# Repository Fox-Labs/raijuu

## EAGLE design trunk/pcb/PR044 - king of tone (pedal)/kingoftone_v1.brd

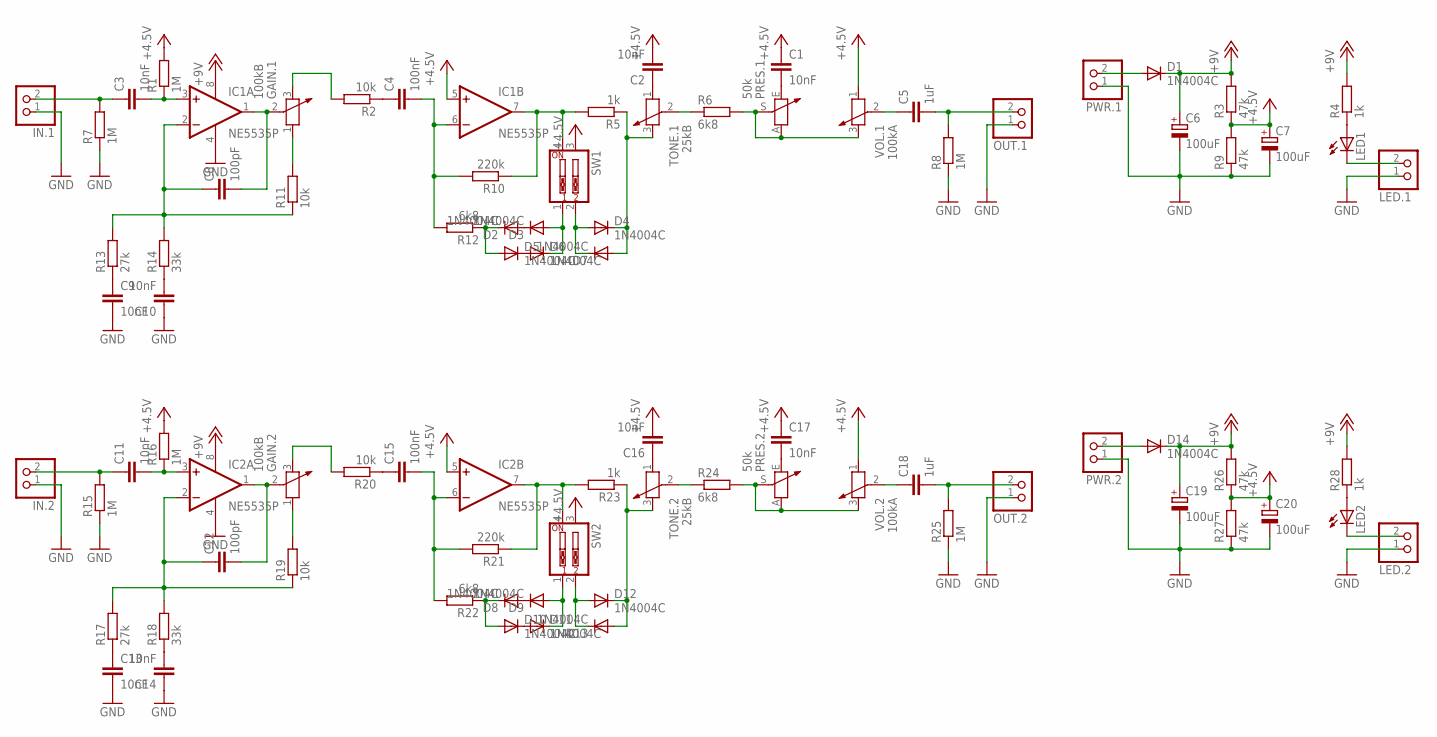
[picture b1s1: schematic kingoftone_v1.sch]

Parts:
C1, C2, C3, C9, C10, C11, C13, C14, C16, C17: 10nF; C050-025X075
C4, C15: 100nF; C050-025X075
C5, C18: 1uF; C050-025X075
C6, C7, C19, C20: 100uF; E2,5-6
C8, C12: 100pF; C050-025X075
D1, D2, D3, D4, D5, D6, D7, D8, D9, D10, D11, D12, D13, D14: 1N4004C; DO41-5
GAIN.1, GAIN.2: 100kB; 1X03
IC1, IC2: NE5535P; DIL08
IN.1, IN.2: PINHD-1X2; 1X02
LED1, LED2: LED3MM
LED.1, LED.2: PINHD-1X2; 1X02
OUT.1, OUT.2: PINHD-1X2; 1X02
PRES.1, PRES.2: 50k; CT6
PWR.1, PWR.2: PINHD-1X2; 1X02
R1, R7, R8, R15, R16, R25: 1M; 0207/5V
R2, R11, R19, R20: 10k; 0207/5V
R3, R9, R26, R27: 47k; 0207/5V
R4, R5, R23, R28: 1k; 0207/5V
R6, R12, R22, R24: 6k8; 0207/5V
R10, R21: 220k; 0207/5V
R13, R17: 27k; 0207/5V
R14, R18: 33k; 0207/5V
SW1, SW2: SW_DIP-2; EDG-02
TONE.1, TONE.2: 25kB; 1X03
VOL.1, VOL.2: 100kA; 1X03

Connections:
+4.5V: C1.1, C2.2, C7.+, C16.2, C17.1, C20.+, IC1.5 (+IN), IC2.5 (+IN), R1.2, R3.1, R9.2, R16.2, R26.1, R27.2, SW1.3, SW2.3, VOL.1.1, VOL.2.1
+9V: C6.+, C19.+, D1.C, D14.C, IC1.8 (V+), IC2.8 (V+), R3.2, R4.2, R26.2, R28.2
GND: C6.-, C7.-, C9.2, C10.1, C13.2, C14.1, C19.-, C20.-, IC1.4 (V-), IC2.4 (V-), IN.1.1, IN.2.1, LED.1.1, LED.2.1, OUT.1.1, OUT.2.1, PWR.1.1, PWR.2.1, R7.1, R8.1, R9.1, R15.1, R25.1, R27.1
unnamed: C3.1, IN.1.2, R7.2
unnamed: C3.2, IC1.3 (+IN), R1.1
unnamed: C8.1, IC1.2 (-IN), R11.1, R13.2, R14.2
unnamed: C8.2, GAIN.1.2 (3), IC1.1 (OUT)
unnamed: C9.1, R13.1
unnamed: C10.2, R14.1
unnamed: GAIN.1.1, R11.2
unnamed: C4.1, R2.1
unnamed: GAIN.1.3 (2), R2.2
unnamed: C4.2, IC1.6 (-IN), R10.2, R12.2
unnamed: IC1.7 (OUT), R5.2, R10.1, SW1.4
unnamed: D2.A, D3.C
unnamed: D2.C, D5.A, R12.1
unnamed: D5.C, D6.A
unnamed: D3.A, D6.C, SW1.1
unnamed: D4.C, D7.A, R5.1, TONE.1.3 (2)
unnamed: D4.A, D7.C, SW1.2
unnamed: C5.1, VOL.1.2 (3)
unnamed: R6.1, TONE.1.2 (3)
unnamed: C2.1, TONE.1.1
unnamed: C1.2, PRES.1.E (2)
unnamed: PRES.1.A (1), PRES.1.S (3), R6.2, VOL.1.3 (2)
unnamed: C5.2, OUT.1.2, R8.2
unnamed: D1.A, PWR.1.2
unnamed: LED1.A, R4.1
unnamed: LED1.K (C), LED.1.2
unnamed: C11.1, IN.2.2, R15.2
unnamed: C11.2, IC2.3 (+IN), R16.1
unnamed: C12.1, IC2.2 (-IN), R17.2, R18.2, R19.1
unnamed: C12.2, GAIN.2.2 (3), IC2.1 (OUT)
unnamed: C13.1, R17.1
unnamed: C14.2, R18.1
unnamed: GAIN.2.1, R19.2
unnamed: C15.1, R20.1
unnamed: GAIN.2.3 (2), R20.2
unnamed: C15.2, IC2.6 (-IN), R21.2, R22.2
unnamed: IC2.7 (OUT), R21.1, R23.2, SW2.4
unnamed: D8.A, D9.C
unnamed: D8.C, D10.A, R22.1
unnamed: D10.C, D11.A
unnamed: D9.A, D11.C, SW2.1
unnamed: D12.A, D13.C, SW2.2
unnamed: R24.1, TONE.2.2 (3)
unnamed: C16.1, TONE.2.1
unnamed: C17.2, PRES.2.E (2)
unnamed: PRES.2.A (1), PRES.2.S (3), R24.2, VOL.2.3 (2)
unnamed: D12.C, D13.A, R23.1, TONE.2.3 (2)
unnamed: C18.1, VOL.2.2 (3)
unnamed: C18.2, OUT.2.2, R25.2
unnamed: D14.A, PWR.2.2
unnamed: LED2.A, R28.1
unnamed: LED2.K (C), LED.2.2

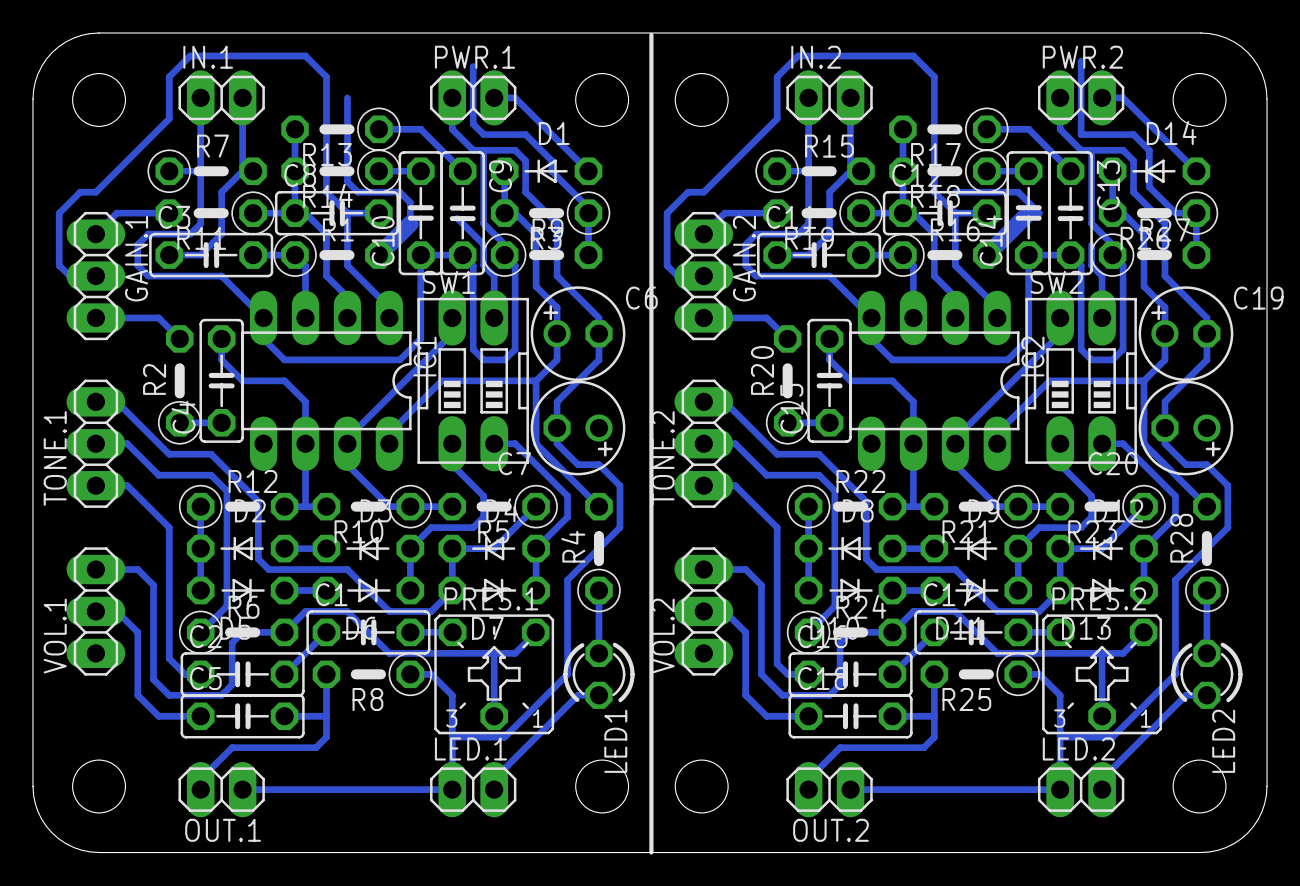
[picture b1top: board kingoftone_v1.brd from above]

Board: 2 copper layers, 74.8 x 49.6 mm, 84 parts (0 on the bottom side), 55 nets.

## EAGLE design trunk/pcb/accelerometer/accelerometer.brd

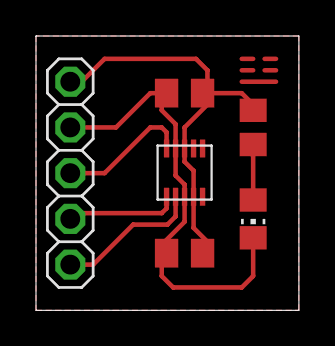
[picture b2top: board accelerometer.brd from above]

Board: 2 copper layers, 14.6 x 15.2 mm, 6 parts (0 on the bottom side), 6 nets.

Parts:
C1, C2: C0805K
JP1: 1X05
LED1: CHIP-LED0805
R1: R0805
U$1: MMA7660DFN-10-HAND; DFN-10-HAND

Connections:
+3V3: C1.1, C2.1, JP1.5, R1.2, U$1.P$3, U$1.P$9
/INT: JP1.3, U$1.P$5
GND: C1.2, C2.2, JP1.4, LED1.C, U$1.P$4, U$1.P$8
unnamed: LED1.A, R1.1
SCL: JP1.2, U$1.P$6
SDA: JP1.1, U$1.P$7

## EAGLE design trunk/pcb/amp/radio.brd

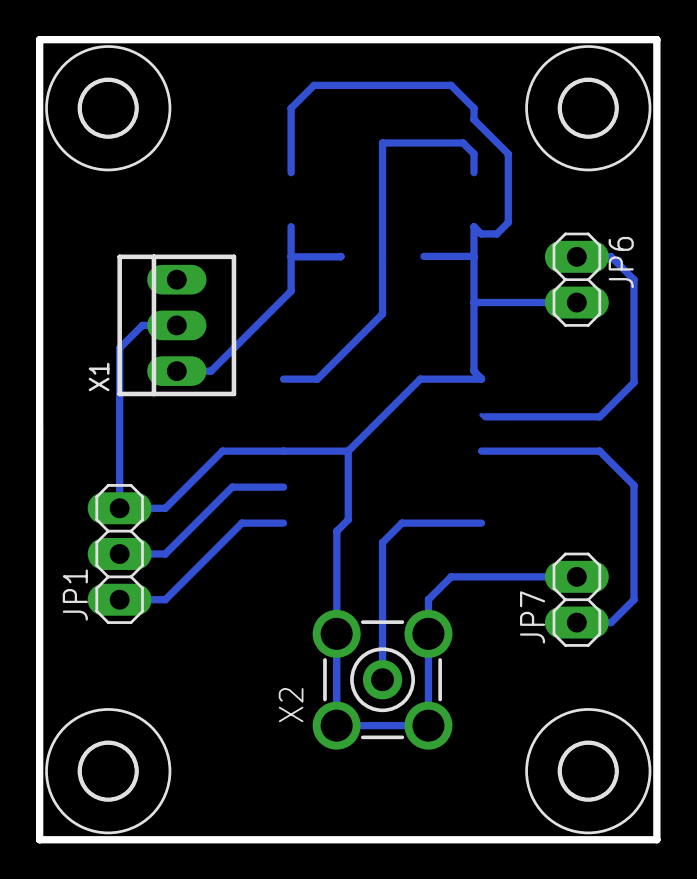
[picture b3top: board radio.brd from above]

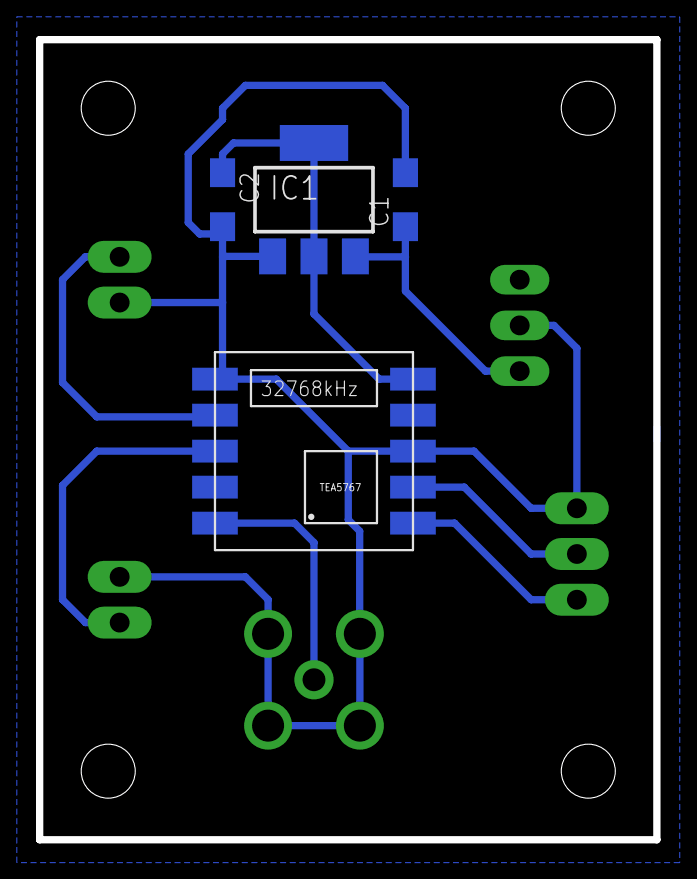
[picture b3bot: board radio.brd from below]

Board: 2 copper layers, 34.3 x 44.5 mm, 13 parts (4 on the bottom side), 8 nets.

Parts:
C1, C2: SMC_A
IC1: LM1117S; SOT223
JP1: 1X03
JP6, JP7: 1X02
U1: TEA5767
U$1, U$2, U$3, U$4: 3,0
X1: 22-23-2031
X2: BU-SMA-V

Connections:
+3V3: C2.+, IC1.2, IC1.4, U1.5
+12V: C1.+, IC1.3, X1.1
GND: C1.-, C2.-, IC1.1, JP1.3, JP6.2, JP7.2, U1.3, U1.6, X1.2, X2.2, X2.3, X2.4, X2.5
unnamed: U1.10, X2.1
OUT_L: JP6.1, U1.7
OUT_R: JP7.1, U1.8
SCL: JP1.2, U1.2
SDA: JP1.1, U1.1

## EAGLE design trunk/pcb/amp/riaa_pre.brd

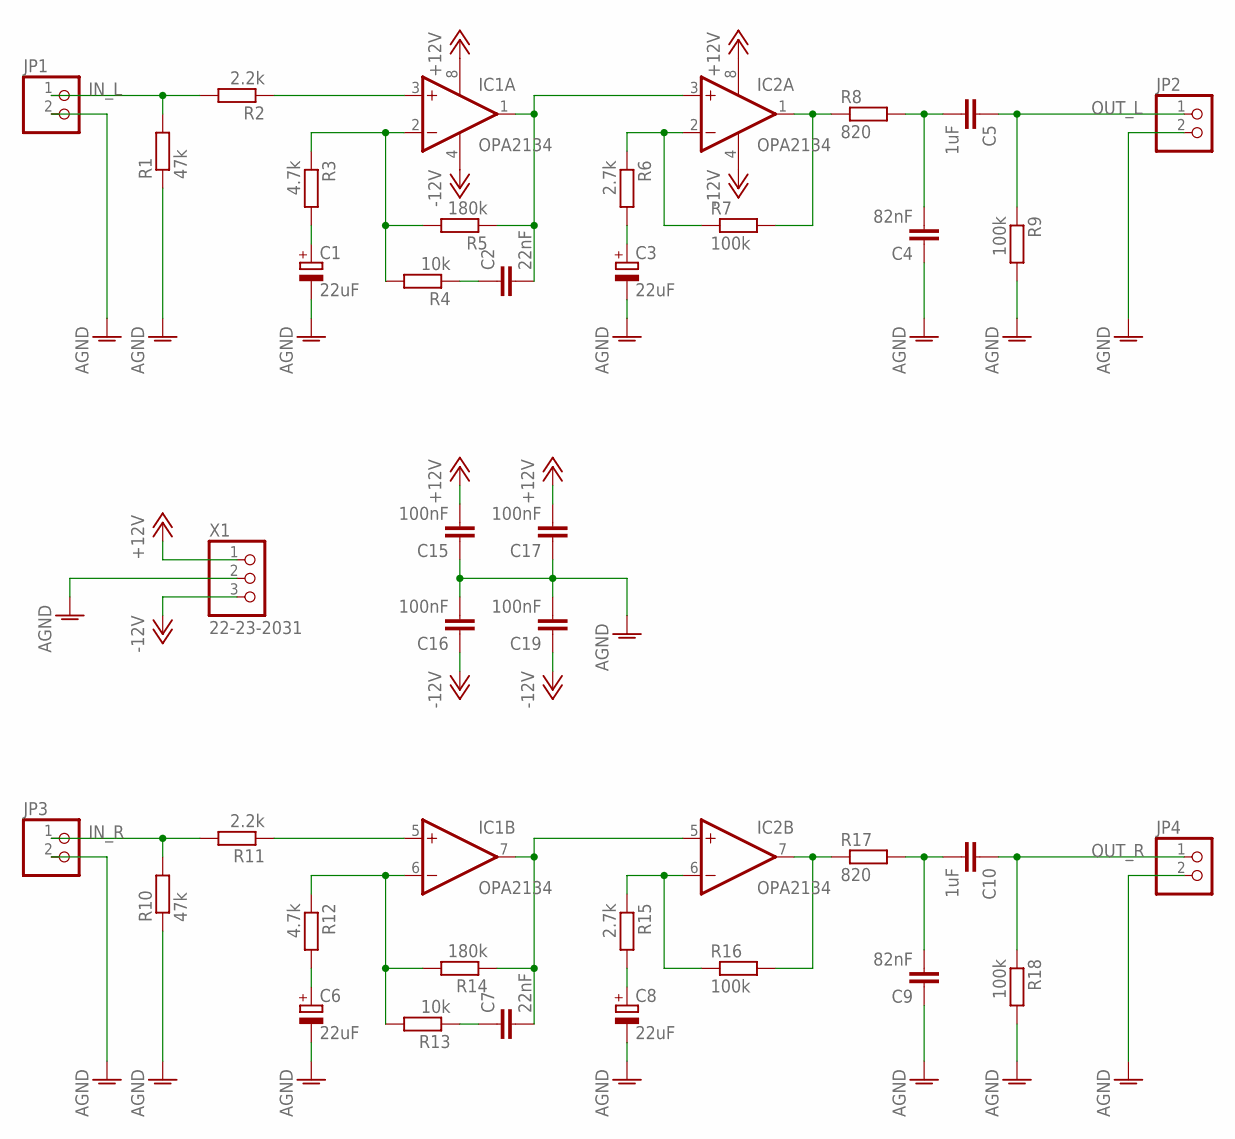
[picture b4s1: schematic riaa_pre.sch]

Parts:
C1, C3, C6, C8: 22uF; E2,5-6
C2, C7: 22nF; C050-025X075
C4, C9: 82nF; C050-025X075
C5, C10: 1uF; C050-025X075
C15, C16, C17, C19: 100nF; C050-025X075
IC1, IC2: OPA2134; DIL08
JP1, JP2, JP3, JP4: PINHD-1X2; 1X02
R1, R10: 47k; 0207/7
R2, R11: 2.2k; 0207/7
R3, R12: 4.7k; 0207/7
R4, R13: 10k; 0207/7
R5, R14: 180k; 0207/7
R6, R15: 2.7k; 0207/7
R7, R9, R16, R18: 100k; 0207/7
R8, R17: 820; 0207/7
X1: 22-23-2031

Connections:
+12V: C15.2, C17.2, IC1.8 (V+), IC2.8 (V+), X1.1
-12V: C16.1, C19.1, IC1.4 (V-), IC2.4 (V-), X1.3
AGND: C1.-, C3.-, C4.1, C6.-, C8.-, C9.1, C15.1, C16.2, C17.1, C19.2, JP1.2, JP2.2, JP3.2, JP4.2, R1.1, R9.2, R10.1, R18.2, X1.2
IN_L: JP1.1, R1.2, R2.2
IN_R: JP3.1, R10.2, R11.2
unnamed: C3.+, R6.2
unnamed: IC1.3 (+IN), R2.1
unnamed: C2.2, IC1.1 (OUT), IC2.3 (+IN), R5.1
unnamed: C4.2, C5.2, R8.2
unnamed: C2.1, R4.1
unnamed: IC1.2 (-IN), R3.1, R4.2, R5.2
unnamed: IC2.6 (-IN), R15.1, R16.1
unnamed: IC2.7 (OUT), R16.2, R17.1
unnamed: IC1.5 (+IN), R11.1
unnamed: C7.2, IC1.7 (OUT), IC2.5 (+IN), R14.1
unnamed: C7.1, R13.1
unnamed: IC1.6 (-IN), R12.1, R13.2, R14.2
unnamed: C6.+, R12.2
unnamed: C8.+, R15.2
unnamed: C9.2, C10.2, R17.2
unnamed: IC2.2 (-IN), R6.1, R7.1
unnamed: IC2.1 (OUT), R7.2, R8.1
unnamed: C1.+, R3.2
OUT_L: C5.1, JP2.1, R9.1
OUT_R: C10.1, JP4.1, R18.1

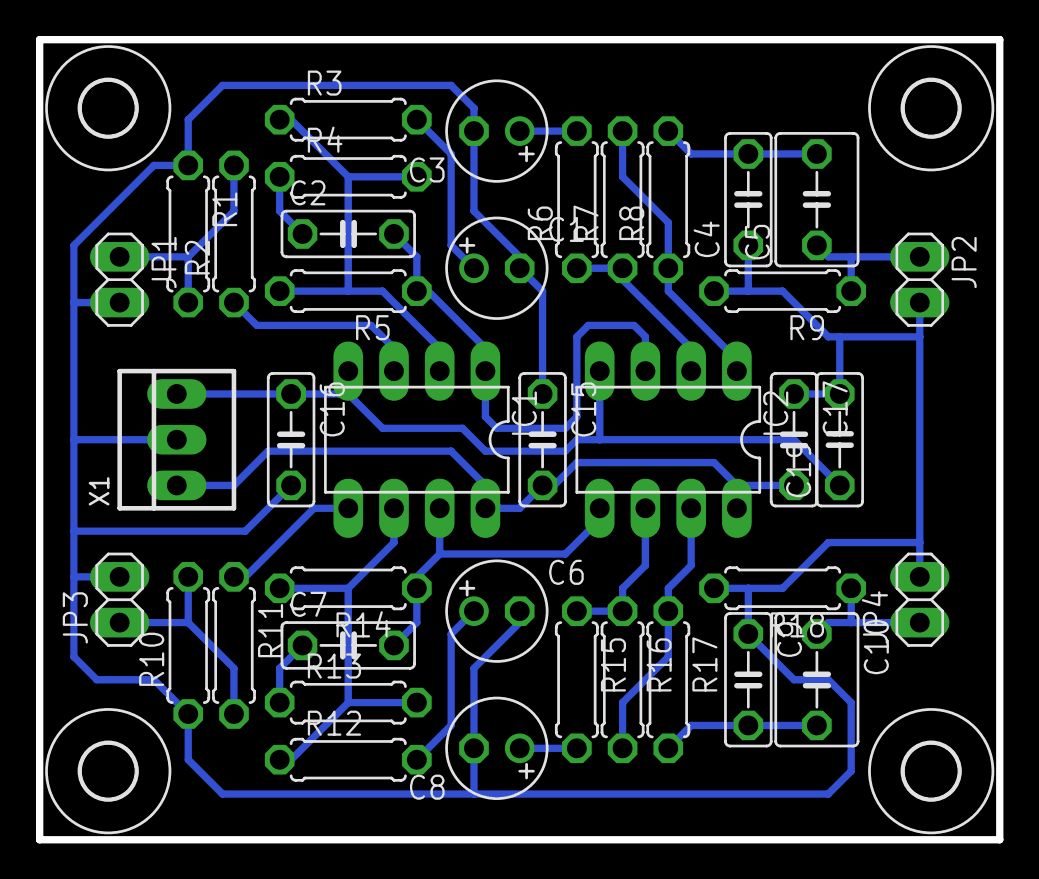
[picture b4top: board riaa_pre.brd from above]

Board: 2 copper layers, 53.3 x 44.5 mm, 43 parts (0 on the bottom side), 25 nets.

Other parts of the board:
U$1, U$2, U$3, U$4: 3,0

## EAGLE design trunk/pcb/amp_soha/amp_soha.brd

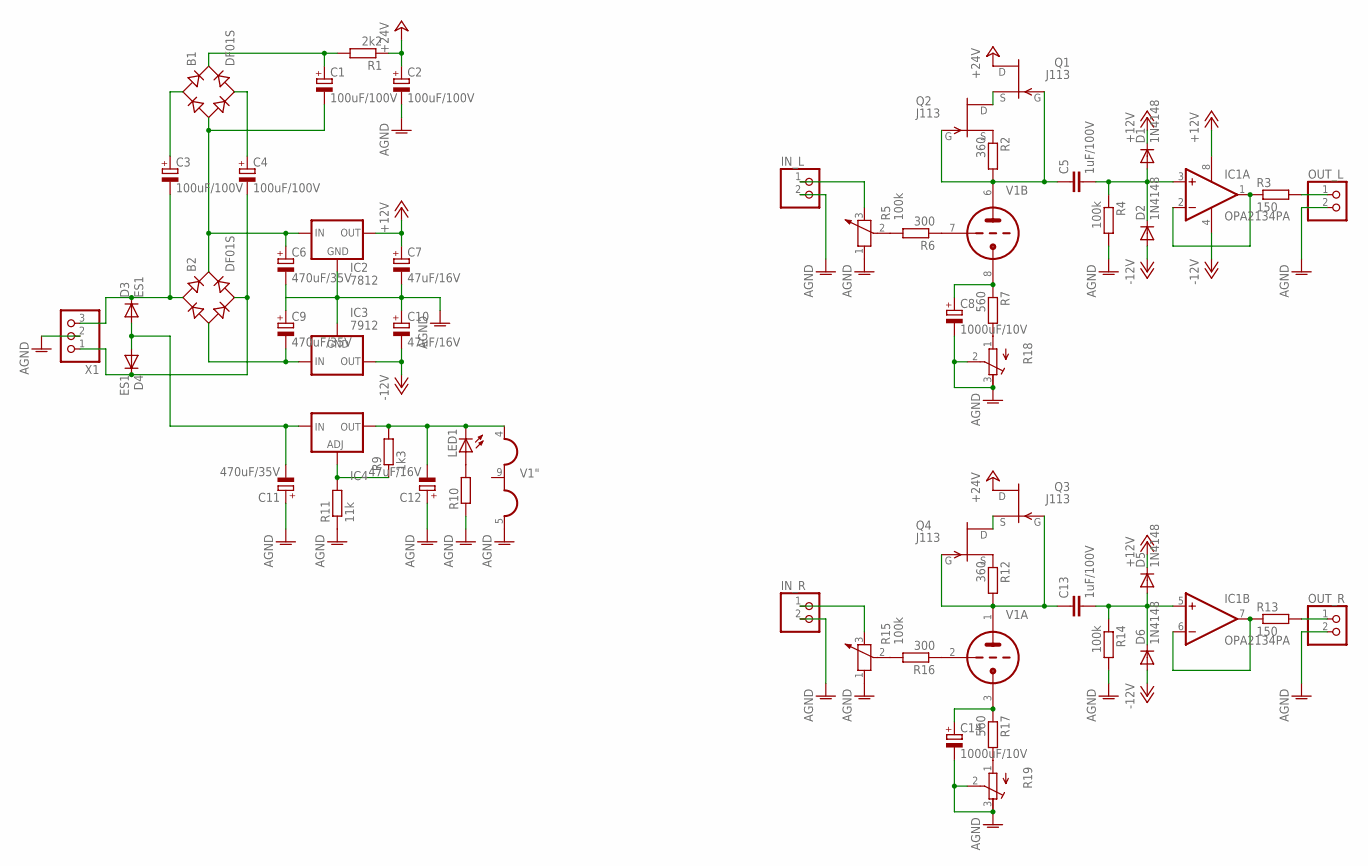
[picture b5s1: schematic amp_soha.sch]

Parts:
B1, B2: DF01S; DFS
C1, C2, C3, C4: 100uF/100V; E5-10,5
C5, C13: 1uF/100V; C150-072X183
C6, C9, C11: 470uF/35V; E5-10,5
C7, C10, C12: 47uF/16V; E2,5-6
C8, C14: 1000uF/10V; E5-10,5
D1, D2, D5, D6: 1N4148; D0805
D3, D4: ES1; DO-214AC
IC1: OPA2134PA; DIL08
IC2: 7812; 78XXS
IC3: 7912; 79XXS
IC4: LM337TS; 337TS
IN_L: PINHD-1X2; 1X02
IN_R: PINHD-1X2; 1X02
LED1: LED5MM
OUT_L: PINHD-1X2; 1X02
OUT_R: PINHD-1X2; 1X02
Q1, Q2, Q3, Q4: J113; TO92
R1: 2k2; R0805
R2, R12: 360; R0805
R3, R13: 150; R0805
R4, R14: 100k; R0805
R5, R15: 100k; 1X03
R6, R16: 300; R0805
R7, R17: 560; R0805
R9: 1k3; R0805
R10: R-EU_; R0805
R11: 11k; R0805
R18, R19: RTRIM329Y; RTRIM3296Y
V1: 12AU7-P; NOVAL
X1: W237-103

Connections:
+12V: C7.+, D1.K (C), D5.K (C), IC1.8 (V+), IC2.OUT
+24V: C2.+, Q1.3 (D), Q3.3 (D), R1.1
-12.6V: C12.-, IC4.3 (OUT), LED1.K (C), R9.2, V1.4 (H1)
-12V: C10.-, D2.A, D6.A, IC1.4 (V-), IC3.OUT
AGND: C2.-, C6.-, C7.-, C8.-, C9.+, C10.+, C11.+, C12.+, C14.-, IC2.GND, IC3.GND, IN_L.2, IN_R.2, OUT_L.2, OUT_R.2, R4.2, R5.1, R10.1, R11.1, R14.2, R15.1, R18.2 (S), R18.3 (E), R19.2 (S), R19.3 (E), V1.5 (H3), X1.2; also elsewhere on the board
unnamed 5: B2.AC1, C3.-, D3.C, X1.3; also elsewhere on the board
unnamed 6: B2.AC2, C4.-, D4.C, X1.1; also elsewhere on the board
unnamed: C11.-, D3.A, D4.A, IC4.2 (IN)
unnamed: IC4.1 (ADJ), R9.1, R11.2
unnamed: B2.-, C9.-, IC3.IN
unnamed: B1.-, B2.+, C1.-, C6.+, IC2.IN
unnamed: LED1.A, R10.2
unnamed: B1.AC1, C3.+
unnamed: B1.AC2, C4.+
unnamed: R16.1, V1.2 (TG)
unnamed: B1.+, C1.+, R1.2
unnamed: IN_L.1, R5.3 (2)
unnamed: R5.2 (3), R6.2
unnamed: R6.1, V1.7 (TG)
unnamed: C8.+, R7.1, V1.8 (TK)
unnamed: Q2.2 (S), R2.1
unnamed: R7.2, R18.1 (A)
unnamed: R17.2, R19.1 (A)
unnamed: C5.1, Q1.1 (G), Q2.1 (G), R2.2, V1.6 (TA)
unnamed: Q1.2 (S), Q2.3 (D)
unnamed: C5.2, D1.A, D2.K (C), IC1.3 (+IN), R4.1
unnamed: IC1.1 (OUT), IC1.2 (-IN), R3.1
unnamed: OUT_L.1, R3.2
unnamed: IN_R.1, R15.3 (2)
unnamed: R15.2 (3), R16.2
unnamed: C14.+, R17.1, V1.3 (TK)
unnamed: C13.1, Q3.1 (G), Q4.1 (G), R12.2, V1.1 (TA)
unnamed: Q4.2 (S), R12.1
unnamed: Q3.2 (S), Q4.3 (D)
unnamed: C13.2, D5.A, D6.K (C), IC1.5 (+IN), R14.1
unnamed: IC1.6 (-IN), IC1.7 (OUT), R13.1
unnamed: OUT_R.1, R13.2

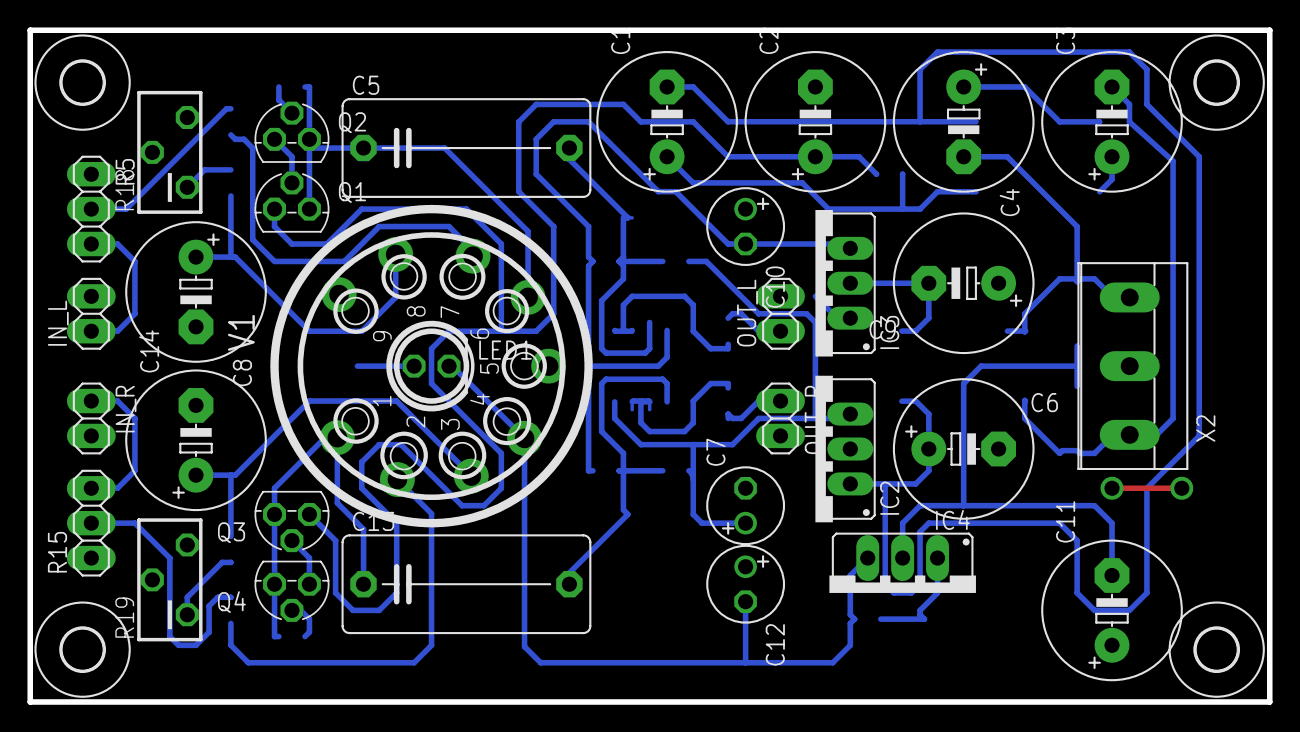
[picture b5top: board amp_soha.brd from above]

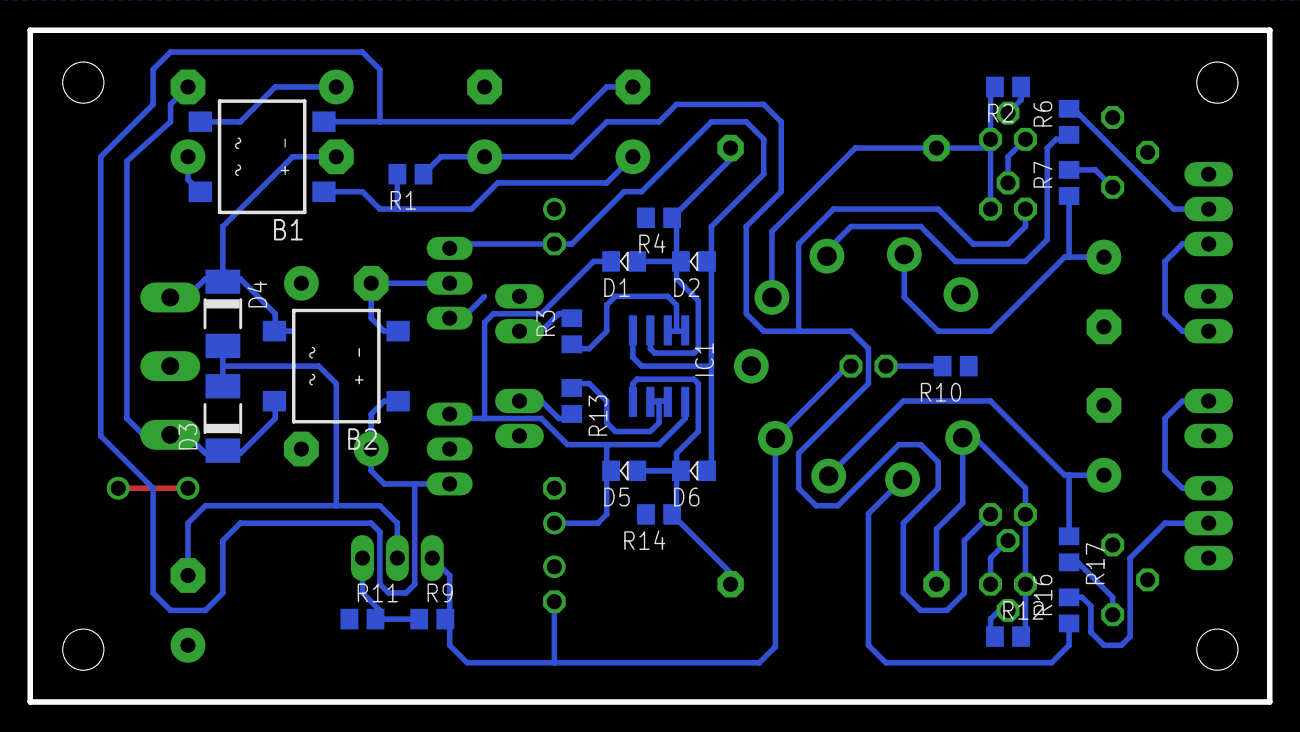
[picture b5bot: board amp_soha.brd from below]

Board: 2 copper layers, 90.2 x 48.9 mm, 59 parts (23 on the bottom side), 37 nets.

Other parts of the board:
U$1, U$2, U$3, U$4: 3,0
X2: W237-103

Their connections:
AGND: X2.2; also elsewhere on the board
unnamed 5: X2.1; also elsewhere on the board
unnamed 6: X2.3; also elsewhere on the board
